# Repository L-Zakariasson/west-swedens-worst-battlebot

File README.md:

This is a school project for my integrated systems course.
Using C and the atmega 328p processor I am creating a very shitty battlebot.

The hardware includes a HC-06 bluetooth module, a 5 to 3,3 V logic converter, and the Motron M3T453 i2c motor controller.
It takes commands from a ps5 controller using a computer running a python script to send commands over BT serial and the bot uses  that to control two motors to provide "Tank" steering and one motor for the weapon.

The chassi is built using Lego.

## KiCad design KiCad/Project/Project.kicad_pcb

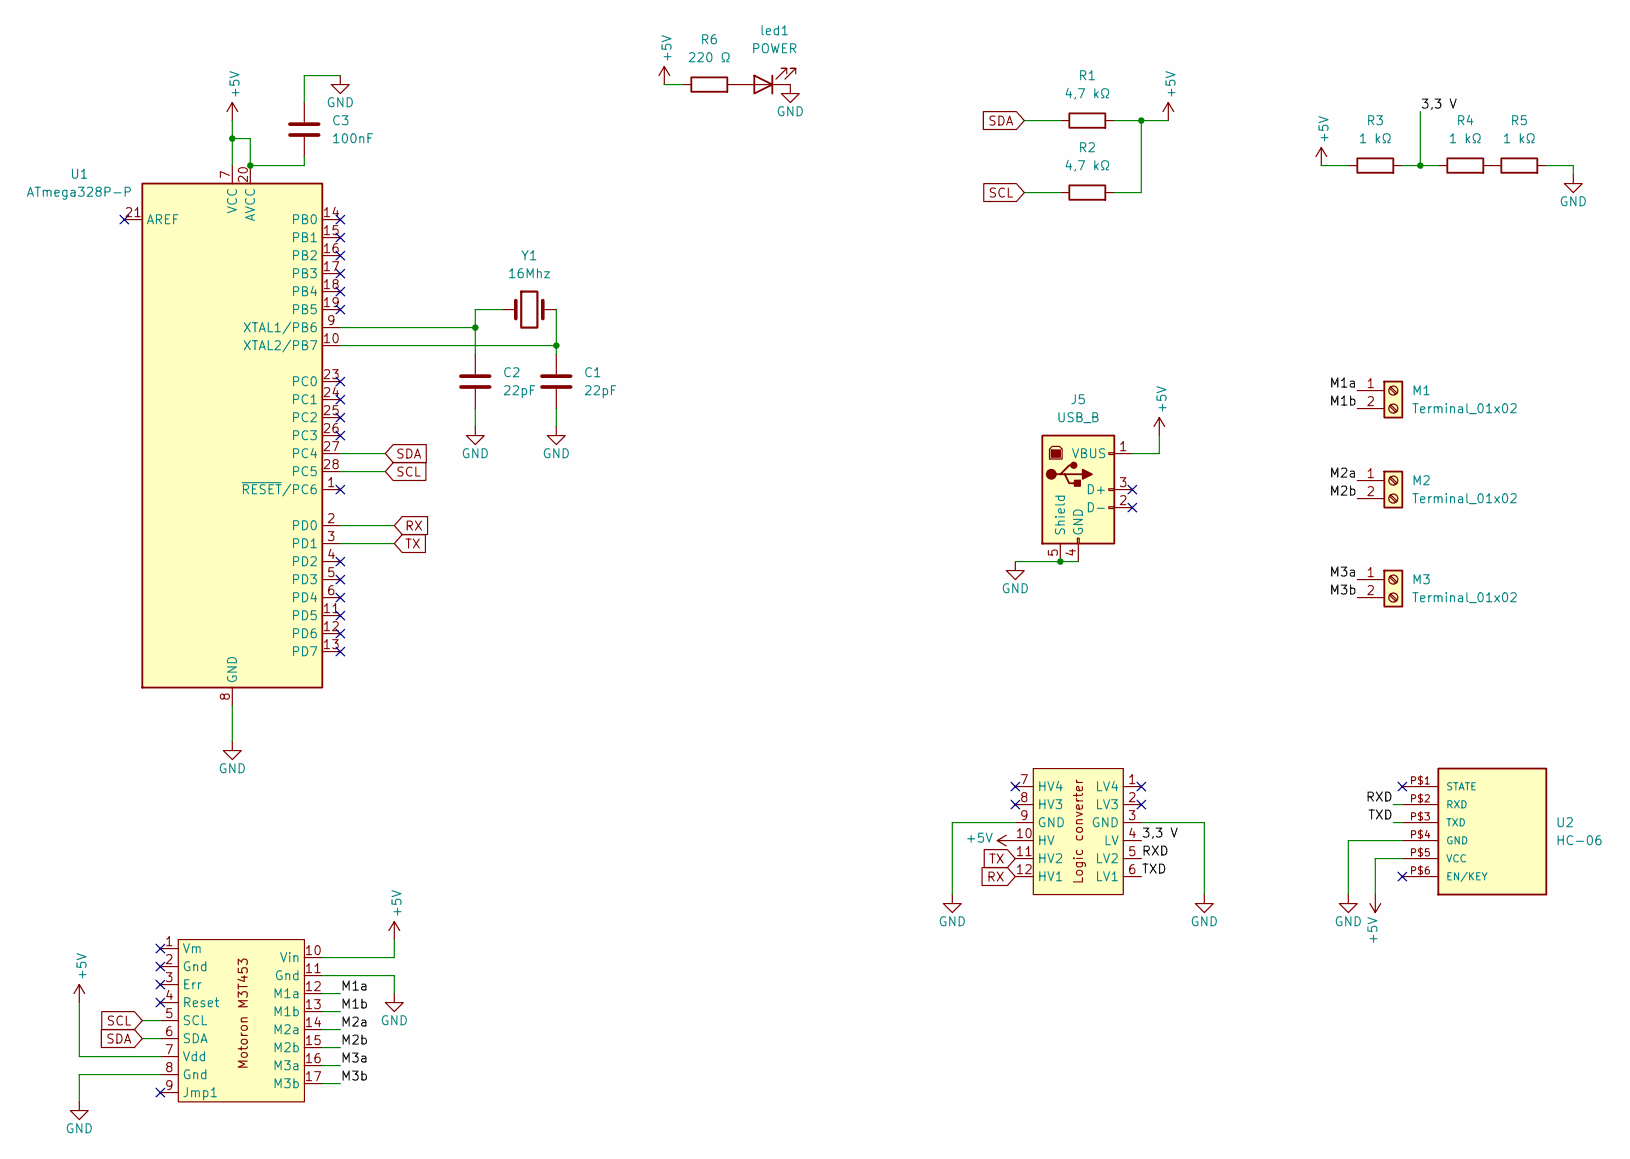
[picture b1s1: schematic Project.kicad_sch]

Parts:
C1, C2: 22pF; C_Disc_D5.0mm_W2.5mm_P2.50mm
C3: 100nF; C_Rect_L7.2mm_W2.5mm_P5.00mm_FKS2_FKP2_MKS2_MKP2
J5: USB_B; USB_B_Lumberg_2411_02_Horizontal
M1, M2, M3: Terminal_01x02; TerminalBlock_MetzConnect_Type094_RT03502HBLU_1x02_P5.00mm_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
R1, R2: 4,7 kΩ; R_Axial_DIN0207_L6.3mm_D2.5mm_P7.62mm_Horizontal
R3, R4, R5: 1 kΩ; R_Axial_DIN0207_L6.3mm_D2.5mm_P7.62mm_Horizontal
R6: 220 Ω; R_Axial_DIN0207_L6.3mm_D2.5mm_P7.62mm_Horizontal
U1: ATmega328P-P; ZIF 28pin den hos elektrokit, maybe
U2: HC-06
U3: motron m3t453
U5: logic converter
Y1: 16Mhz; Crystal_HC49-U_Vertical
led1: POWER; LED_D5.0mm

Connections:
+5V: C3.2, J5.1 (VBUS), R1.2, R2.2, R3.1, R6.1, U1.7 (VCC), U1.20 (AVCC), U2.P$5 (VCC), U3.7 (Vdd), U3.10 (Vin), U5.10 (HV)
/3,3 V: R3.2, R4.1, U5.4 (LV)
/M1a: M1.1, U3.12 (M1a)
/M1b: M1.2, U3.13 (M1b)
/M2a: M2.1, U3.14 (M2a)
/M2b: M2.2, U3.15 (M2b)
/M3a: M3.1, U3.16 (M3a)
/M3b: M3.2, U3.17 (M3b)
/RXD: U2.P$2 (RXD), U5.5 (LV2)
/TXD: U2.P$3 (TXD), U5.6 (LV1)
GND: C1.2, C2.2, C3.1, J5.4 (GND), J5.5 (Shield), R5.2, U1.8 (GND), U1.22 (GND), U2.P$4 (GND), U3.8 (Gnd), U3.11 (Gnd), U5.3 (GND), U5.9 (GND), led1.1 (K)
unnamed: R4.2, R5.1
unnamed: C2.1, U1.9 (XTAL1/PB6), Y1.1
unnamed: C1.1, U1.10 (XTAL2/PB7), Y1.2
unnamed: R6.2, led1.2 (A)
RX: U1.2 (PD0), U5.12 (HV1)
SCL: R2.1, U1.28 (PC5), U3.5 (SCL)
SDA: R1.1, U1.27 (PC4), U3.6 (SDA)
TX: U1.3 (PD1), U5.11 (HV2)

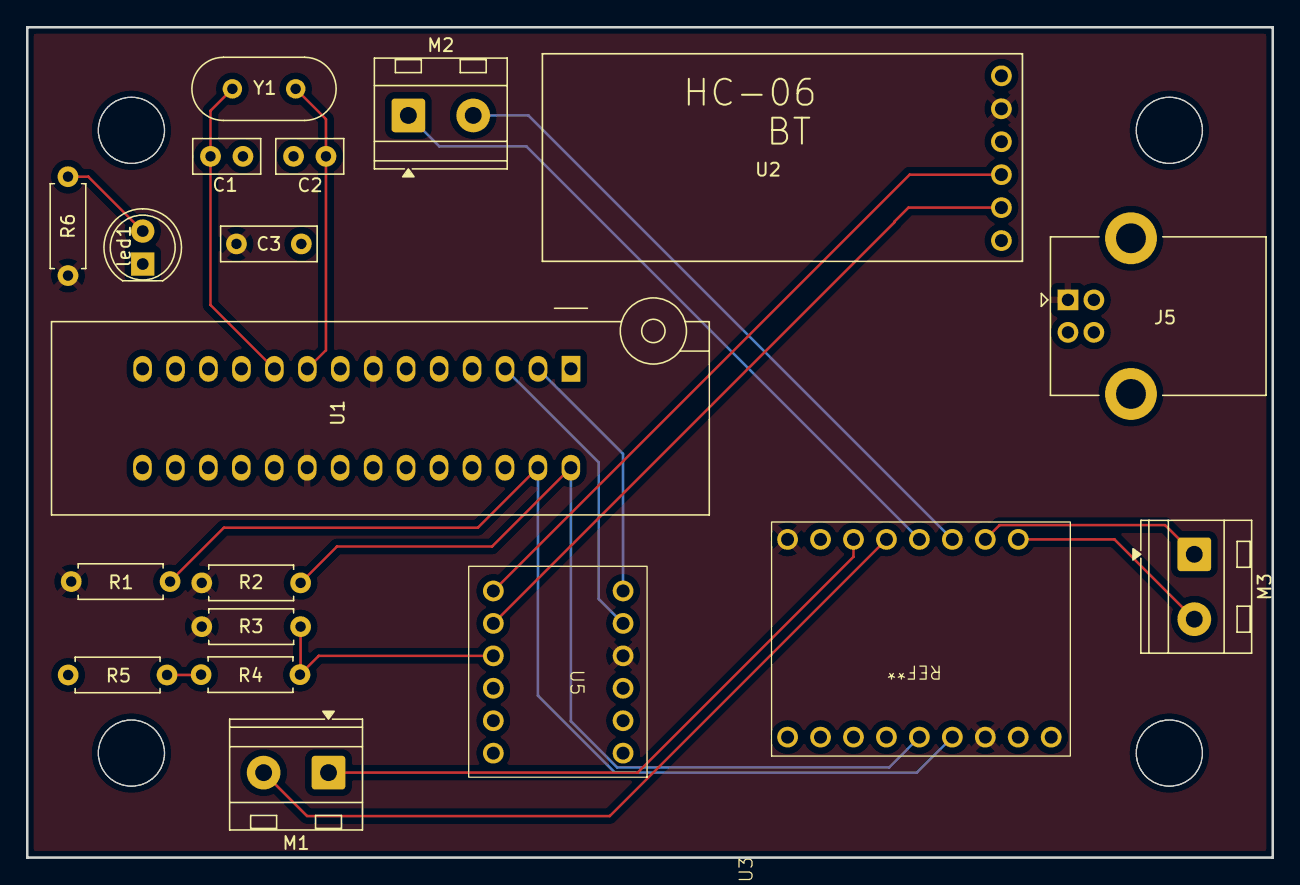
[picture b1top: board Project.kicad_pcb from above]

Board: 2 copper layers, 96.0 x 64.0 mm, 19 parts (0 on the bottom side), 19 nets.

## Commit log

2026-03-11 v1.0
    uploading working v1 in case i fuck up the code
2026-03-12 completed KiCad
    completed KiCad with garber and drill files
2026-03-12 Update KiCad.zip
    now its done...
2026-03-12 added src,drivers and header file
    Cleaned up code and created dedicated files
2026-03-12 Create README.md
    quick readme, much quality
2026-03-12 optimized variables
    optimized variables and moved some stuff around
2026-03-19 v1.1
    added a python script co get controller input and controll robot using two joysticks
2026-03-23 1.3
    cleaned up old comments from code
2026-03-26 Update README.md
    i cant spell
2026-03-30 v1.4
    fixed spelling
2026-03-30 v1.2
    Updated capacitor and resistor values
2026-03-30 v 1.3
    fixed pads om BT footprint
2026-03-30 v 1.4
    updated capacitor values, for real this time
